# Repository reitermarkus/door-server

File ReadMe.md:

# Door Server

## Development

```
cargo run --release
```

## Deployment

```
ansible-playbook -i inventory.yml playbook.yml
```

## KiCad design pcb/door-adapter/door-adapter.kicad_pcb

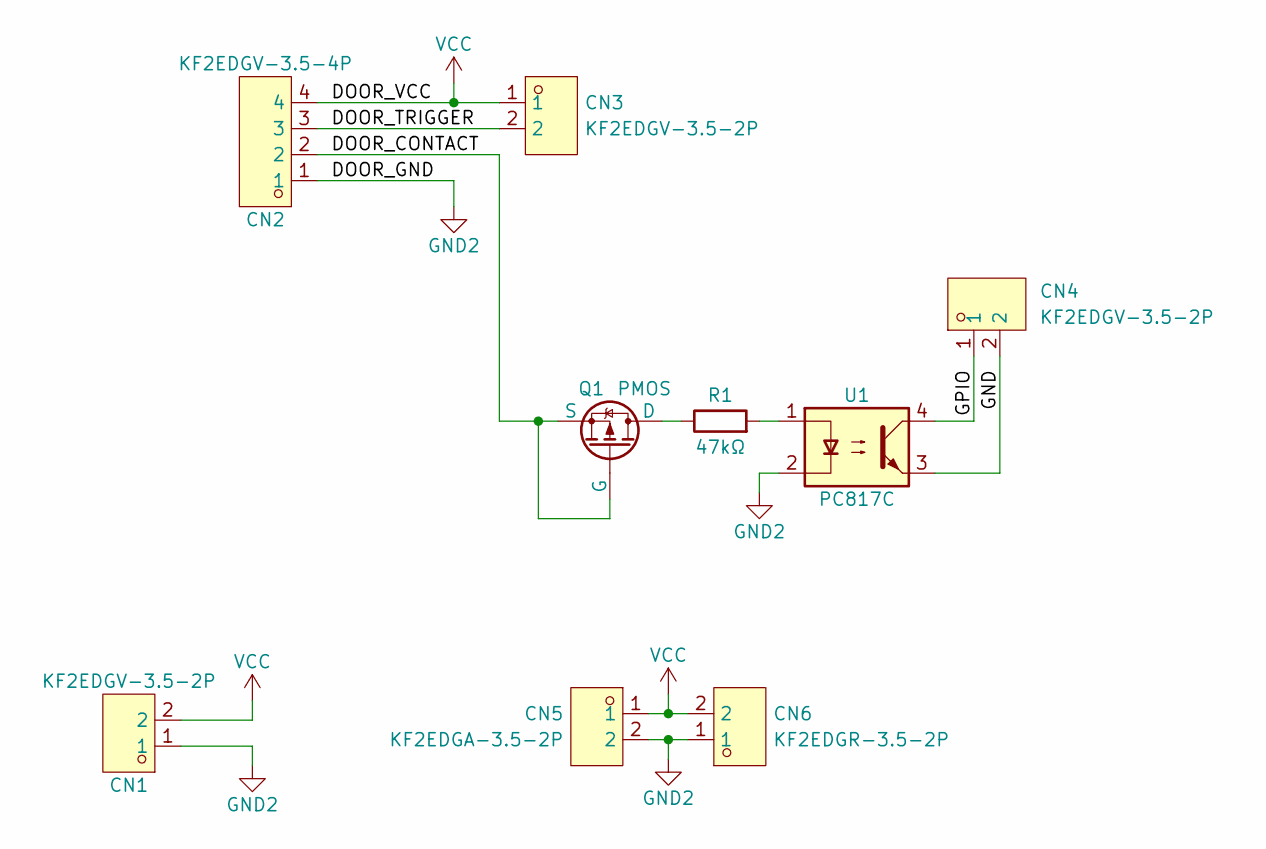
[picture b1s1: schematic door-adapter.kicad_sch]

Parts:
CN1, CN3, CN4: KF2EDGV-3.5-2P; CONN-TH_2P_P3.50_KF2EDGV-3.5-2P; LCSC Part C441321
CN2: KF2EDGV-3.5-4P; CONN-TH_4P-P3.50_KF2EDGV-3.5-4P; LCSC Part C441323
CN5: KF2EDGA-3.5-2P; CONN-TH_2P_P3.50_KF2EDGA-3.5-2P; LCSC Part C6394073
CN6: KF2EDGR-3.5-2P; CONN-TH_2P-P3.50_KF2EDGR-3.5-2P; LCSC Part C441171
Q1: PMOS; X1-DFN1006-3_L1.0-W0.6-P0.35-BR; LCSC Part C3282097
R1: 47kΩ; R_0201_0603Metric; LCSC Part C18164341
U1: PC817C; OPTO-SMD-4_L4.6-W6.5-P2.54-LS10.3-TL; LCSC Part C3025164

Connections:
/DOOR_CONTACT: CN2.2, Q1.2 (G), Q1.3 (S)
/DOOR_TRIGGER: CN2.3, CN3.2
/GND: CN4.2, U1.3
/GPIO: CN4.1, U1.4
GND2: CN1.1, CN2.1, CN5.2, CN6.1, U1.2
unnamed: Q1.1 (D), R1.1
unnamed: R1.2, U1.1
VCC: CN1.2, CN2.4, CN3.1, CN5.1, CN6.2

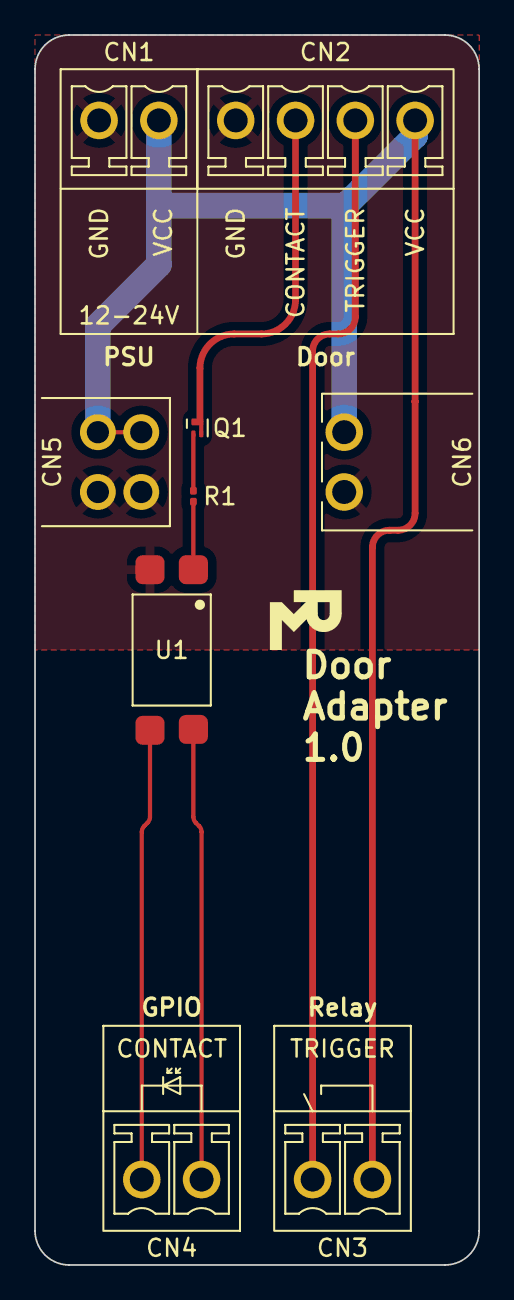
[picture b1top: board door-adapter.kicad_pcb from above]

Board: 2 copper layers, 26.0 x 72.0 mm, 9 parts (0 on the bottom side), 8 nets.

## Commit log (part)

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2021-08-29 Implement door server.
2021-09-02 Remove unneeded `unwrap`s.
2021-09-02 Move delay to `stop` method.
2021-09-02 Don't set property in action.
2021-09-02 Use debounced pin.
2021-09-04 Add custom debouncing to support rising and falling edges.
2021-09-06 Add LED test.
2021-09-06 Set LEDs based on door states.
2021-09-10 Refactor LEDs.
2021-09-10 Set unused LEDs.
2021-09-11 Adjust LED colors.
2021-09-13 Update `embedded-hal` dependency.
2021-09-13 Change target.
2021-09-13 Fix `setup_spi` task.
2021-09-26 Wait for network.
2021-09-26 Update dependencies.
2021-09-26 Enable network wait service.
2021-10-09 Add finger scan events.
2021-10-14 Fix garage door opening/closing on reboot.
2021-10-14 Add logging for garage door button.
2021-10-17 Add Bticino configurator values.
2021-11-03 Add door bell button.
2021-12-02 Fix compilation.
2021-12-02 Refactor build/deployment script.
2021-12-02 Move `run.sh`.
2021-12-02 Don't set linker explicitly.
2022-03-04 Add renovate.json
2022-03-05 Add CI workflow.
2022-03-05 Don't publish crate.
2022-03-05 Patch `rppal`.
2022-03-05 Update Rust crate actix-rt to v2
2022-03-05 Update inventory.
2022-03-05 Revert "Update Rust crate actix-rt to v2"
    This reverts commit f4811908569abd9d6edca1bc3378905ef4344ca6.
2022-03-13 Update `actix-rt`.
2022-03-13 Disable `webthing` patch.
2022-04-20 Update Rust crate uuid to v1
2022-09-10 Update to 2021 edition.
2022-09-10 Fix indentation.
2022-09-10 Tweak debouncing.
2023-11-11 Increase debounce time.
2023-11-11 Fix formatting.
2023-11-11 Update dependencies and fix clippy warnings.
2023-11-28 Update to new pinout.
2023-11-29 Fix SPI frequency.
2023-11-29 Use `ws2812_spi::hosted::Ws2812`.
2023-11-29 Update `embedded-hal`.
2023-11-29 Update Rust crate embedded-hal to 1.0.0-rc
2023-11-29 Add PCB.
2023-11-29 Add PCB project file.
2023-11-30 Improve PCB layout and connectors.
2023-12-03 Add power supply to PCB.
2023-12-03 Add PCB design rules.
2023-12-03 Add Door Adapter board.
2023-12-03 Fix part number.
2023-12-03 Add order number placeholder.
2023-12-04 Use more `async`.
2024-01-09 Update Rust crate embedded-hal-0 to v1
2024-06-15 Allow changing port.
2024-06-15 Fix code style.
2024-06-15 Fix clippy warnings.
2024-06-15 alpine
2024-06-15 Add more build targets.
2025-04-19 Remove unneeded dependency.
2025-04-19 Remove `WaveshareRelay` struct.
2025-04-19 Re-add dependency for example.
2025-04-19 Release 0.2.0.
2026-01-02 Switch to ESPHome.
2026-01-03 Improve door state updates.
2026-01-03 Improve garage door state.
2026-02-15 Improve threading.
2026-02-15 Add balcony door.
2026-03-26 Pin reitermarkus/.github action to ff02c9a
2026-04-02 Revert "Pin reitermarkus/.github action to ff02c9a"
    This reverts commit c49b396fb798369cc9c79c58c283fea453fb925a.
2026-04-02 Pin reitermarkus/.github action to b51c8a3
2026-04-02 Lock file maintenance
